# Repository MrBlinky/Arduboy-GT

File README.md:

# Arduboy-GT

Homemade Arduboy using custom PCB, modules and all through hole parts and a 1.54" OLED display.

For more info check out the [Hackster.io Project](https://www.hackster.io/mrblinky/diy-arduboy-gt-2e4824)

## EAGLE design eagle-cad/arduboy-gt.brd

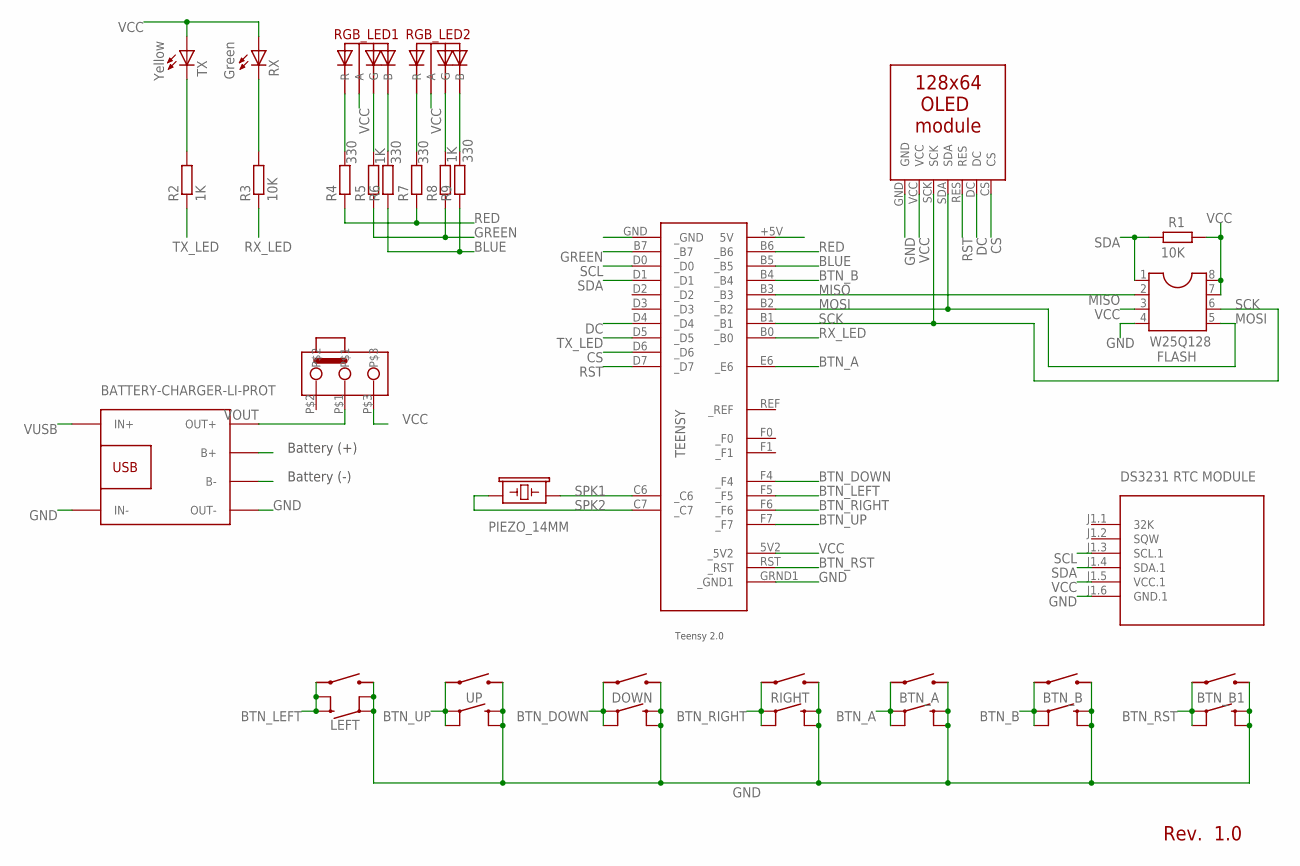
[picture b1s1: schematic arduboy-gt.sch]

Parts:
BTN_A: MOMENTARY-SWITCH-SPST-PTH-6.0MM; TACTILE_SWITCH_PTH_6.0MM
BTN_A_: KAIHLMICROSWITCH
BTN_B, BTN_B1: MOMENTARY-SWITCH-SPST-PTH-6.0MM; TACTILE_SWITCH_PTH_6.0MM
BTN_B_, BTN_B_1: KAIHLMICROSWITCH
DOWN: MOMENTARY-SWITCH-SPST-PTH-6.0MM; TACTILE_SWITCH_PTH_6.0MM
DOWN_: KAIHLMICROSWITCH
FLASH: W25Q128; DIL08
LEFT: MOMENTARY-SWITCH-SPST-PTH-6.0MM; TACTILE_SWITCH_PTH_6.0MM
LEFT_: KAIHLMICROSWITCH
R1, R3: 10K; 0204/7
R2, R5, R8: 1K; 0204/7
R4, R6, R7, R9: 330; 0204/7
RGB_LED1, RGB_LED2: 5MMRGBLED-CA; LED5MMRGB
RIGHT: MOMENTARY-SWITCH-SPST-PTH-6.0MM; TACTILE_SWITCH_PTH_6.0MM
RIGHT_: KAIHLMICROSWITCH
RX: TLLG4400; LED3MM
SG1: PIEZO_14MM
TX: TLLY4400; LED3MM
U$1: OLED
U$2: SWITCH
U$3: BATTERY-CHARGER-LI-PROT
U$6: DS3231 RTC MODULE; RTC-DS3231-AT24C32
UP: MOMENTARY-SWITCH-SPST-PTH-6.0MM; TACTILE_SWITCH_PTH_6.0MM
UP_: KAIHLMICROSWITCH
_1: TEENSY

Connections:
BLUE: R6.1, R9.1, _1.B5 (_B5)
BTN_A: BTN_A.1, BTN_A.2, BTN_A_.P$1, _1.E6 (_E6)
BTN_B: BTN_B.1, BTN_B.2, BTN_B_.P$1, _1.B4 (_B4)
BTN_DOWN: DOWN.1, DOWN.2, DOWN_.P$1, _1.F4 (_F4)
BTN_LEFT: LEFT.3, LEFT.4, LEFT_.P$1, _1.F5 (_F5)
BTN_RIGHT: RIGHT.1, RIGHT.2, RIGHT_.P$1, _1.F6 (_F6)
BTN_RST: BTN_B1.1, BTN_B1.2, BTN_B_1.P$1, _1.RST (_RST)
BTN_UP: UP.1, UP.2, UP_.P$1, _1.F7 (_F7)
CS: U$1.CS, _1.D6 (_D6)
DC: U$1.DC, _1.D4 (_D4)
GND: BTN_A.3, BTN_A.4, BTN_A_.P$2, BTN_B.3, BTN_B.4, BTN_B1.3, BTN_B1.4, BTN_B_.P$2, BTN_B_1.P$2, DOWN.3, DOWN.4, DOWN_.P$2, FLASH.4, LEFT.1, LEFT.2, LEFT_.P$2, RIGHT.3, RIGHT.4, RIGHT_.P$2, U$1.GND, U$3.IN-, U$3.OUT-, U$6.J1.6 (GND.1), UP.3, UP.4, UP_.P$2, _1.GND (_GND), _1.GRND1 (_GND1)
GREEN: R5.1, R8.1, _1.B7 (_B7)
MISO: FLASH.2, _1.B3 (_B3)
MOSI: FLASH.5, U$1.SDA, _1.B2 (_B2)
unnamed: R7.2, RGB_LED2.R$1 (R)
unnamed: R8.2, RGB_LED2.G$1 (G)
unnamed: R9.2, RGB_LED2.B$1 (B)
unnamed: R6.2, RGB_LED1.B$1 (B)
unnamed: R5.2, RGB_LED1.G$1 (G)
unnamed: R4.2, RGB_LED1.R$1 (R)
RED: R4.1, R7.1, _1.B6 (_B6)
RST: U$1.RES, _1.D7 (_D7)
RX_LED: R3.1, _1.B0 (_B0)
RX_LED_R: R3.2, RX.K (C)
SCK: FLASH.6, U$1.SCK, _1.B1 (_B1)
SCL: U$6.J1.3 (SCL.1), _1.D0 (_D0)
SDA: FLASH.1, R1.2, U$6.J1.4 (SDA.1), _1.D1 (_D1)
SPK1: SG1.P$2, _1.C6 (_C6)
SPK2: SG1.P$1, _1.C7 (_C7)
TX_LED: R2.1, _1.D5 (_D5)
TX_LED_R: R2.2, TX.K (C)
VCC: FLASH.3, FLASH.7, FLASH.8, R1.1, RGB_LED1.C$1 (A), RGB_LED2.C$1 (A), RX.A, TX.A, U$1.VCC, U$2.P$3, U$6.J1.5 (VCC.1), _1.5V2 (_5V2), _1.+5V (5V)
VOUT: U$2.P$1, U$3.OUT+
VUSB: U$3.IN+

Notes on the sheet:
Battery (-)
Battery (+)
Green
Yellow
Rev. 1.0

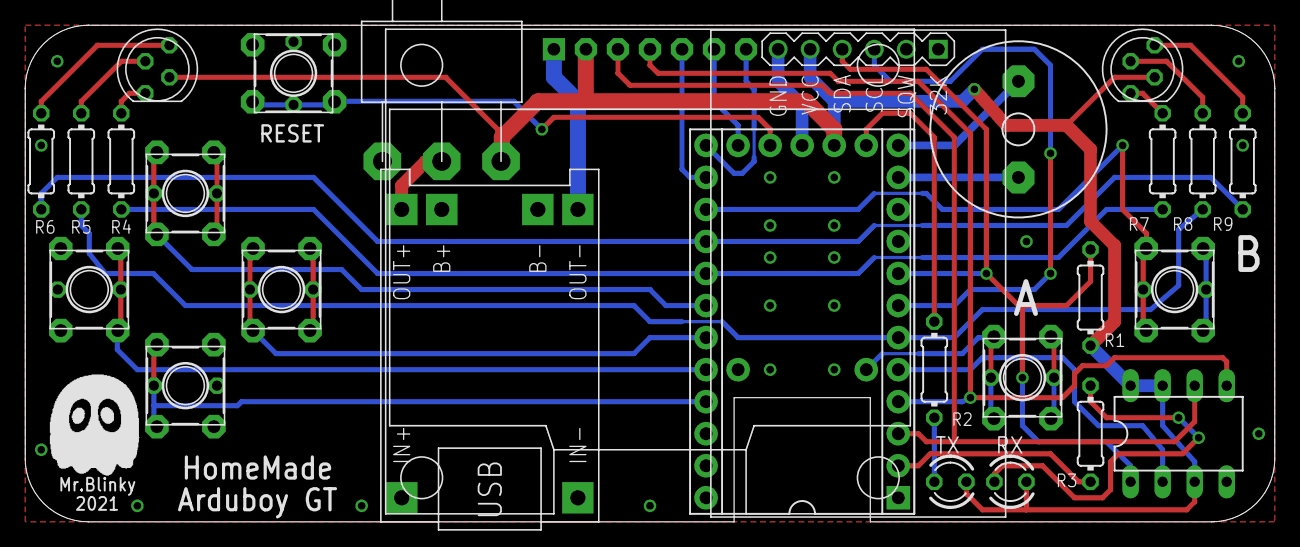
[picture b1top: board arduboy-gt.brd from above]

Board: 2 copper layers, 99.1 x 39.4 mm, 34 parts (0 on the bottom side), 33 nets.

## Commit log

2021-06-28 Add Eagle files and test sketch
2021-06-29 add oshpark pcb images
2021-11-26 Add images

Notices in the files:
parts and their libraries:
diy-modules: Released under the Creative Commons Attribution 4.0 International License: http://creativecommons.org/licenses/by/4.0
teensy: Licensed Under Creative Commons Attribution-ShareAlike 3.0 Unported (CC BY-SA 3.0)
